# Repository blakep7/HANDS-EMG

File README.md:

# HANDS-EMG

**HANDS-EMG** is a real-time embedded system designed to read a user's EMG signals and classify their hand movements.

## Project Description
A battery-powered surface electromyography (sEMG) sensor system designed to classify hand movements based on the wearer's muscle activity.
The device utilizes four channels of wet electrodes placed on the user's forearm to capture sEMG signals.
These signals are processed through our procured analog front-end module operating at 2000Hz.
The digitized signals are transmitted to our microcontroller via SPI, where a machine learning algorithm classifies the hand movements based on a pre-trained model.
The system will output the movement classifications via USB, which can be visualized on a PC simulator.
Designed for efficiency, the device operates at a voltage of 3.7V provided by a rechargeable lithium polymer battery for portability.
The current ML model only classifies 3 hand movements: Wrist Flexion, Wrist Extension, and Fist Clench.

## Videos
[Project Overview (Entire Design Process)](https://www.youtube.com/watch?v=24S8prk70tI)

[Demo Video](https://www.youtube.com/watch?v=GeJwxeHSsiM)

## Team

- Blake Pearson
- Noah Marosok
- Kelly Hubbard
- Jayden Sumbillo
- Kirk Young

## About
Developed at **San Diego State University**.

**College of Engineering** -- **Department of Electrical and Computer Engineering (ECE)**

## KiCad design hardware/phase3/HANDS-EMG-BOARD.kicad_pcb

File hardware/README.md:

# PCB Projects
Welcome to the PCB repository! This folder contains four PCB phases:

- **Phase 1**
- **Phase 2**
- **Phase 3**

Each project is fully designed in KiCad and includes schematics, PCB layouts, and 3D models.

## Phase Descriptions

### Phase 1

**Description:**  
Contains 3 PCBs, each designed with a specific purpose.

**Key Components:**
- PMIC Board: Provide power to the following two PCBs
- ADS1299 Board: Our AFE board that handles processing and digitizing EMG signals
- STM32 Board: Our uC board that handles classification and compute

**Warnings**
- Do not use this phase, it taught us alot about PCB design but is riddled with issues
- PMIC Board is less than 50% functional.
    - 3.3V line is actually 3.6V which is absolute maximum of STM32
    - -2.5V line is unstable, due to only using a charge pump without a LDO after
- ADS1299 Board is not functional
    - Unknown issue in PCB design that kills the IC.

### Phase 2

**Description:**  
The team's attempt at a fully integrated PCB design.

**Warnings**
- Do not use this phase
- Board's USB to UART is not functional, no communication possible
- SWD footprint is mirrored

### Phase 3 (Final Phase)

**Description:**
The team's final design. Focused on simplicity, cost, and small dimensions. Fully tested and working

**Key Components**
- STM32L0: Our main compute, has the ML model and classifies the signals
- ADS1299: Our AFE, handles amplifying and digitizing our EMG signals
- FT231X: USB->UART IC for simple communication between STM32 and PC

---

## 3D Model Previews

**Final PCB 3D View:**  

---

## How to Open the Projects

1. Install [KiCad](https://kicad.org/) (v9).
2. Open KiCad and navigate to the respective folder (`phase3`).
3. Open the `.kicad_pro` project file inside each folder.

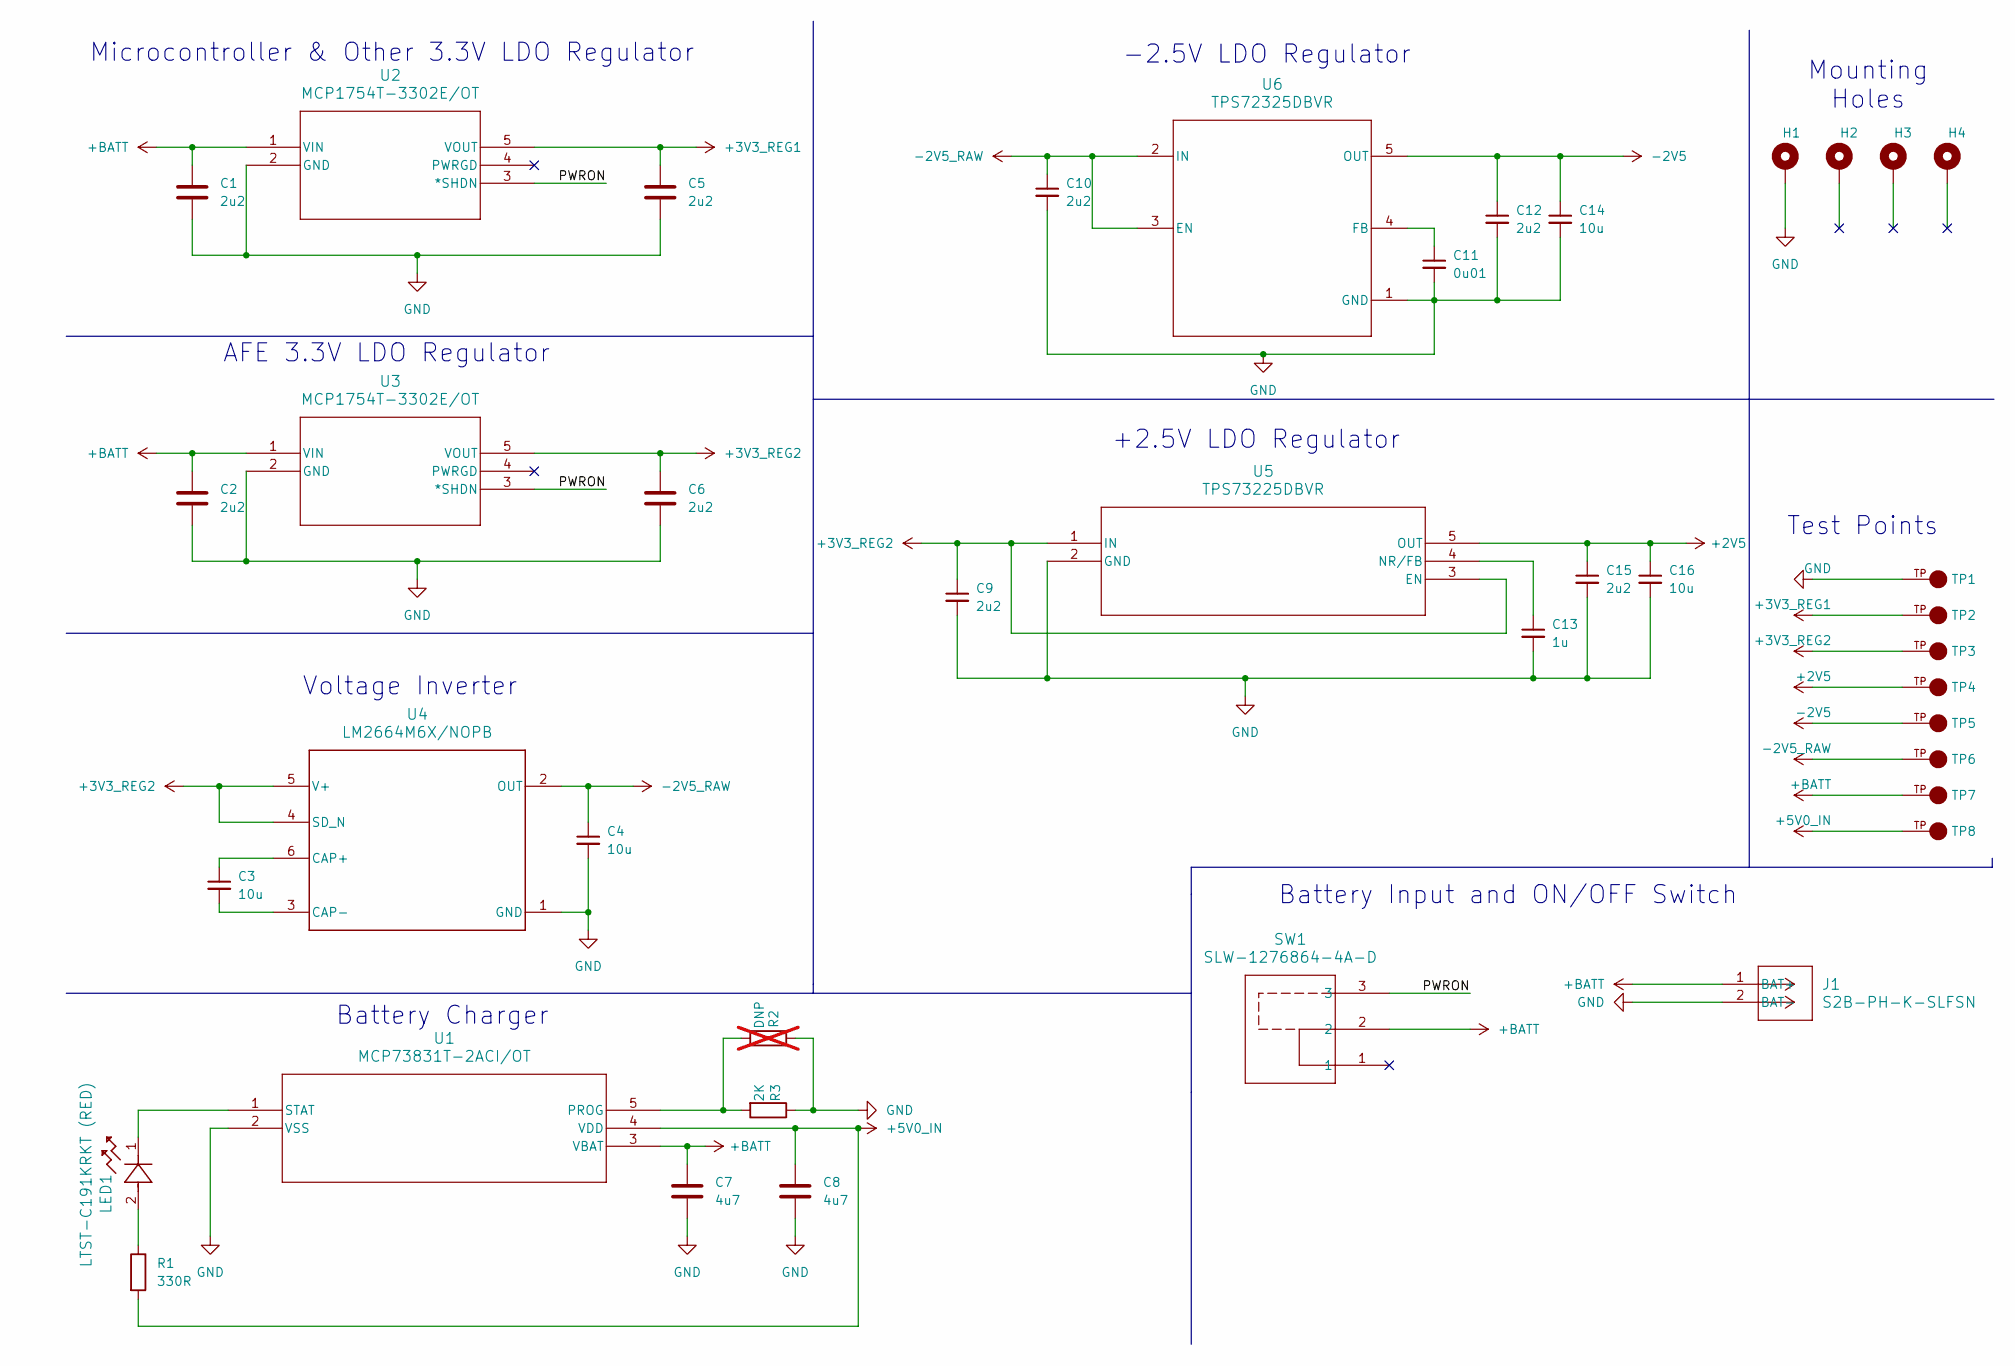
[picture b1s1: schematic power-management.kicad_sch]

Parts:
C1, C2, C5, C6, C9, C10, C12, C15: 2u2; C_0402_1005Metric
C3, C4, C14, C16: 10u; C_0603_1608Metric
C7, C8: 4u7; C_0603_1608Metric
C11: 0u01; C_0402_1005Metric
C13: 1u; C_0402_1005Metric
H1, H2, H3, H4: MountingHole_Pad; MountingHole_2.2mm_M2_Pad
J1: S2B-PH-K-SLFSN; S2B-PH-K-S
LED1: LTST-C191KRKT (RED); LTST-C191KRKT
R1: 330R; R_0603_1608Metric
R2: DNP; R_0603_1608Metric; not fitted
R3: 2K; R_0603_1608Metric
SW1: SLW-1276864-4A-D
TP1, TP2, TP3, TP4, TP5, TP6, TP7, TP8: 5015; PARTREV F
U1: MCP73831T-2ACI/OT; MCP73831T-2ACI-OT
U2, U3: MCP1754T-3302E/OT; MCP1754T-3302E-OT
U4: LM2664M6X/NOPB; LM2664M6X-NOPB
U5: TPS73225DBVR
U6: TPS72325DBVR

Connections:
+2V5: C15.1, C16.1, TP4.TP, U5.5 (OUT); also elsewhere on the board
+3V3_REG1: C5.1, TP2.TP, U2.5 (VOUT); also elsewhere on the board
+3V3_REG2: C6.1, C9.1, TP3.TP, U3.5 (VOUT), U4.4 (SD_N), U4.5 (V+), U5.1 (IN), U5.3 (EN); also elsewhere on the board
+5V0_IN: C8.1, R1.2, TP8.TP, U1.4 (VDD); also elsewhere on the board
+BATT: C1.1, C2.1, C7.1, J1.1 (BAT+), SW1.2, TP7.TP, U1.3 (VBAT), U2.1 (VIN), U3.1 (VIN)
-2V5: C12.1, C14.1, TP5.TP, U6.5 (OUT); also elsewhere on the board
-2V5_RAW: C4.1, C10.1, TP6.TP, U4.2 (OUT), U6.2 (IN), U6.3 (EN)
/Power-Management/PWRON: SW1.3, U2.3 (*SHDN), U3.3 (*SHDN)
GND: C1.2, C2.2, C4.2, C5.2, C6.2, C7.2, C8.2, C9.2, C10.2, C11.2, C12.2, C13.2, C14.2, C15.2, C16.2, H1.1, J1.2 (BAT-), R2.1, R3.1, TP1.TP, U1.2 (VSS), U2.2 (GND), U3.2 (GND), U4.1 (GND), U5.2 (GND), U6.1 (GND); also elsewhere on the board
unnamed: LED1.2, R1.1
unnamed: R2.2, R3.2, U1.5 (PROG)
unnamed: LED1.1, U1.1 (STAT)
unnamed: C3.1, U4.6 (CAP+)
unnamed: C3.2, U4.3 (CAP-)
unnamed: C13.1, U5.4 (NR/FB)
unnamed: C11.1, U6.4 (FB)

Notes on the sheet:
Battery Charger
+2.5V LDO Regulator
AFE 3.3V LDO Regulator
Test Points
Mounting Holes
-2.5V LDO Regulator
Voltage Inverter
Microcontroller & Other 3.3V LDO Regulator
Battery Input and ON/OFF Switch

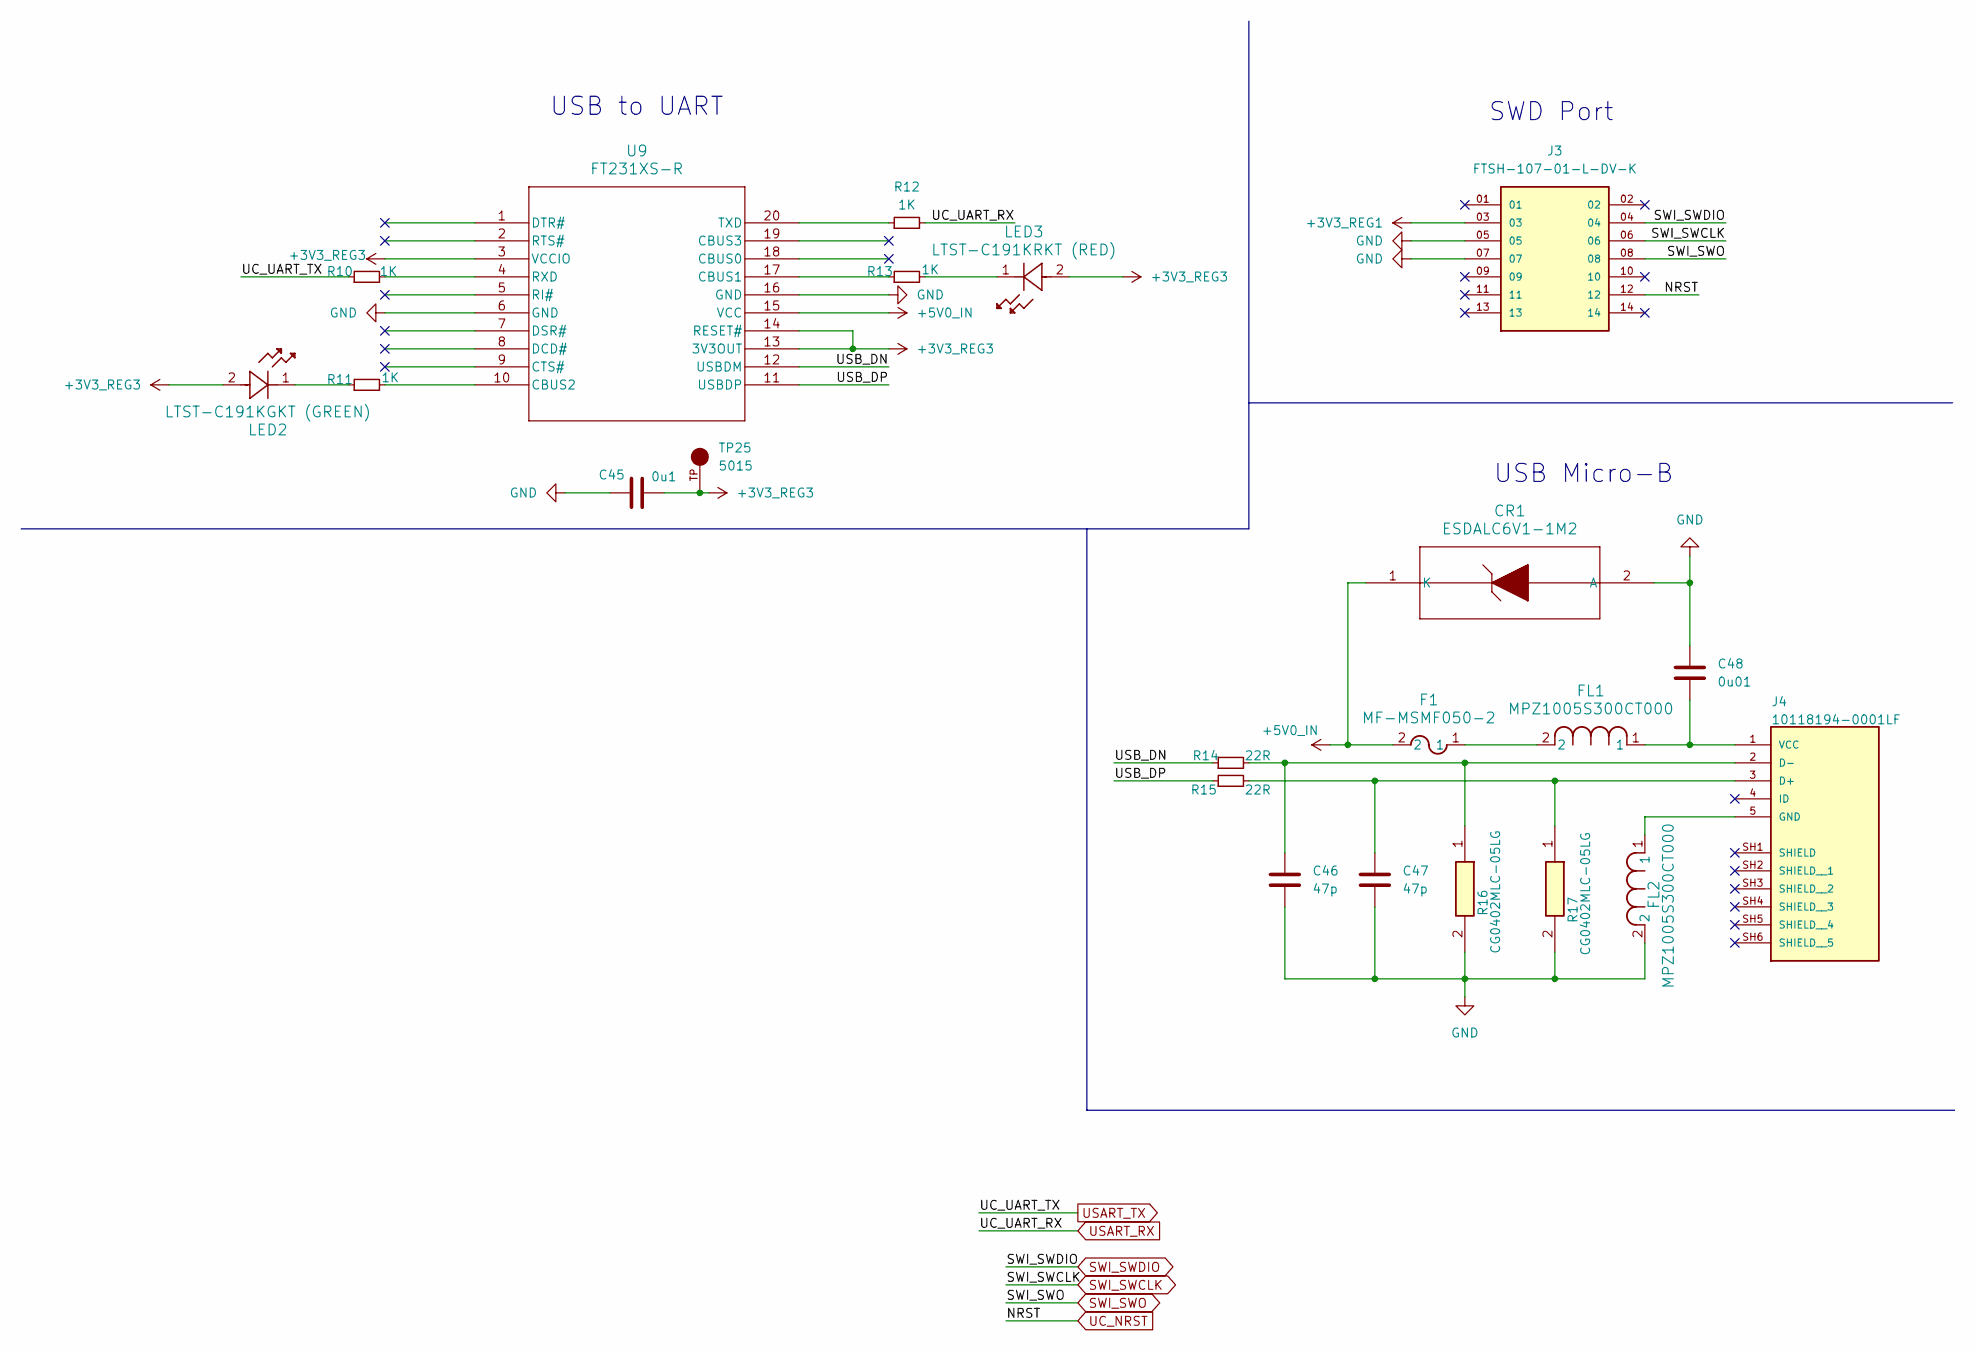
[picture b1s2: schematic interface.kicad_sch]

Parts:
C45: 0u1; C_0402_1005Metric
C46, C47: 47p; C_0402_1005Metric
C48: 0u01; C_0402_1005Metric
CR1: ESDALC6V1-1M2
F1: MF-MSMF050-2
FL1, FL2: MPZ1005S300CT000
J3: FTSH-107-01-L-DV-K; PARTREV R
J4: 10118194-0001LF; PARTREV D
LED2: LTST-C191KGKT (GREEN); LTST-C191KGKT
LED3: LTST-C191KRKT (RED); LTST-C191KRKT
R10, R11, R12, R13: 1K; R_0603_1608Metric
R14, R15: 22R; R_0402_1005Metric
R16, R17: CG0402MLC-05LG
TP25: 5015; PARTREV F
U9: FT231XS-R

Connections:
+3V3_REG1: J3.03; also elsewhere on the board
+3V3_REG3: C45.2, LED2.2, LED3.2, TP25.TP, U9.3 (VCCIO), U9.13 (3V3OUT), U9.14 (RESET#)
+5V0_IN: CR1.1 (K), F1.2, U9.15 (VCC); also elsewhere on the board
/Interface/USB_DN: R14.1, U9.12 (USBDM)
/Interface/USB_DP: R15.1, U9.11 (USBDP)
GND: C45.1, C46.2, C47.2, C48.1, CR1.2 (A), FL2.2, J3.05, J3.07, R16.2, R17.2, U9.6 (GND), U9.16 (GND); also elsewhere on the board
unnamed: F1.1, FL1.2
unnamed: C47.1, J4.3 (D+), R15.2, R17.1
unnamed: C46.1, J4.2 (D-), R14.2, R16.1
unnamed: FL2.1, J4.5 (GND)
unnamed: C48.2, FL1.1, J4.1 (VCC)
unnamed: LED2.1, R11.1
unnamed: LED3.1, R13.2
unnamed: R13.1, U9.17 (CBUS1)
unnamed: R11.2, U9.10 (CBUS2)
unnamed: R10.2, U9.4 (RXD)
unnamed: R12.1, U9.20 (TXD)
SWI_SWCLK: J3.06; also elsewhere on the board
SWI_SWDIO: J3.04; also elsewhere on the board
SWI_SWO: J3.08; also elsewhere on the board
UC_NRST: J3.12; also elsewhere on the board
USART_RX: R12.2; also elsewhere on the board
USART_TX: R10.1; also elsewhere on the board

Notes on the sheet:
USB Micro-B
USB to UART
SWD Port

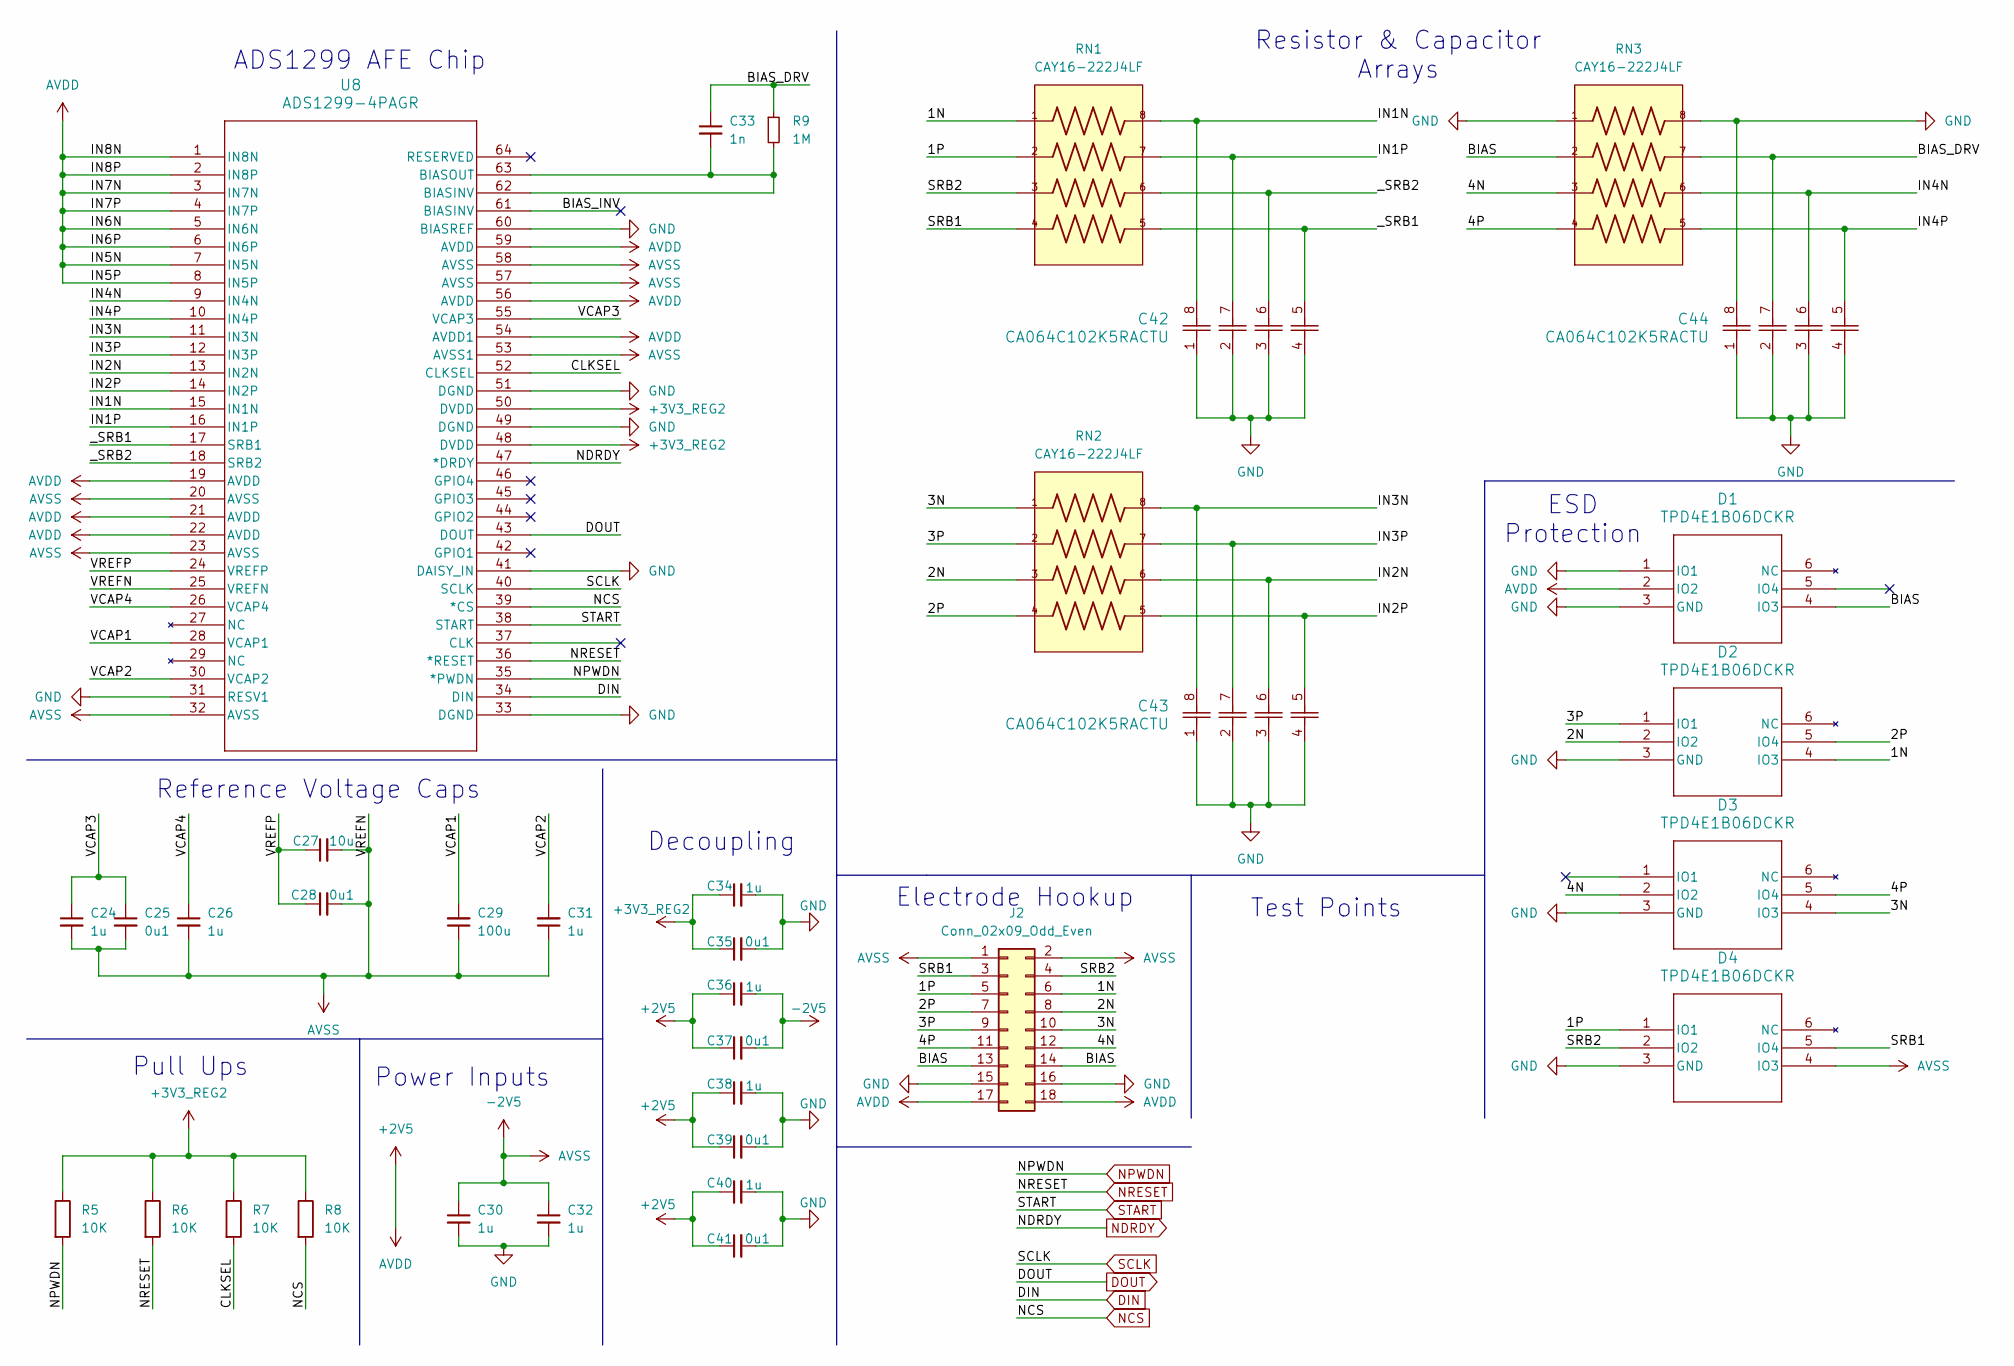
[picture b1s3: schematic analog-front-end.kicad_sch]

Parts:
C24, C26, C30, C31, C32, C34, C36, C38, C40: 1u; C_0402_1005Metric
C25, C28, C35, C37, C39, C41: 0u1; C_0402_1005Metric
C27: 10u; C_0603_1608Metric
C29: 100u; C_1206_3216Metric
C33: 1n; C_0402_1005Metric
C42, C43, C44: CA064C102K5RACTU; CA064C102K5RAC7800
D1, D2, D3, D4: TPD4E1B06DCKR
J2: Conn_02x09_Odd_Even; PinHeader_2x09_P2.54mm_Horizontal
R5, R6, R7, R8: 10K; R_0402_1005Metric
R9: 1M; R_0402_1005Metric
RN1, RN2, RN3: CAY16-222J4LF
U8: ADS1299-4PAGR

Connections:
+2V5: C36.1, C37.1, C38.1, C39.1, C40.1, C41.1, D1.2 (IO2), J2.17, J2.18, U8.1 (IN8N), U8.2 (IN8P), U8.3 (IN7N), U8.4 (IN7P), U8.5 (IN6N), U8.6 (IN6P), U8.7 (IN5N), U8.8 (IN5P), U8.19 (AVDD), U8.21 (AVDD), U8.22 (AVDD), U8.54 (AVDD1), U8.56 (AVDD), U8.59 (AVDD); also elsewhere on the board
+3V3_REG2: C34.1, C35.1, R5.1, R6.1, R7.1, R8.1, U8.48 (DVDD), U8.50 (DVDD); also elsewhere on the board
-2V5: C24.2, C25.2, C26.2, C27.2, C28.2, C29.1, C30.1, C31.1, C32.1, C36.2, C37.2, D4.4 (IO3), J2.1, J2.2, U8.20 (AVSS), U8.23 (AVSS), U8.25 (VREFN), U8.32 (AVSS), U8.53 (AVSS1), U8.57 (AVSS), U8.58 (AVSS); also elsewhere on the board
/Analog-Front-End/1N: D2.4 (IO3), J2.6, RN1.1
/Analog-Front-End/1P: D4.1 (IO1), J2.5, RN1.2
/Analog-Front-End/2N: D2.2 (IO2), J2.8, RN2.3
/Analog-Front-End/2P: D2.5 (IO4), J2.7, RN2.4
/Analog-Front-End/3N: D3.4 (IO3), J2.10, RN2.1
/Analog-Front-End/3P: D2.1 (IO1), J2.9, RN2.2
/Analog-Front-End/4N: D3.2 (IO2), J2.12, RN3.3
/Analog-Front-End/4P: D3.5 (IO4), J2.11, RN3.4
/Analog-Front-End/BIAS: D1.4 (IO3), J2.13, J2.14, RN3.2
/Analog-Front-End/BIAS_DRV: C33.1, C44.7, R9.1, RN3.7
/Analog-Front-End/BIAS_INV: U8.61 (BIASINV)
/Analog-Front-End/CLKSEL: R7.2, U8.52 (CLKSEL)
/Analog-Front-End/IN1N: C42.8, RN1.8, U8.15 (IN1N)
/Analog-Front-End/IN1P: C42.7, RN1.7, U8.16 (IN1P)
/Analog-Front-End/IN2N: C43.6, RN2.6, U8.13 (IN2N)
/Analog-Front-End/IN2P: C43.5, RN2.5, U8.14 (IN2P)
/Analog-Front-End/IN3N: C43.8, RN2.8, U8.11 (IN3N)
/Analog-Front-End/IN3P: C43.7, RN2.7, U8.12 (IN3P)
/Analog-Front-End/IN4N: C44.6, RN3.6, U8.9 (IN4N)
/Analog-Front-End/IN4P: C44.5, RN3.5, U8.10 (IN4P)
/Analog-Front-End/SRB1: D4.5 (IO4), J2.3, RN1.4
/Analog-Front-End/SRB2: D4.2 (IO2), J2.4, RN1.3
/Analog-Front-End/VCAP1: C29.2, U8.28 (VCAP1)
/Analog-Front-End/VCAP2: C31.2, U8.30 (VCAP2)
/Analog-Front-End/VCAP3: C24.1, C25.1, U8.55 (VCAP3)
/Analog-Front-End/VCAP4: C26.1, U8.26 (VCAP4)
/Analog-Front-End/VREFP: C27.1, C28.1, U8.24 (VREFP)
/Analog-Front-End/_SRB1: C42.5, RN1.5, U8.17 (SRB1)
/Analog-Front-End/_SRB2: C42.6, RN1.6, U8.18 (SRB2)
DIN: U8.34 (DIN); also elsewhere on the board
DOUT: U8.43 (DOUT); also elsewhere on the board
GND: C30.2, C32.2, C34.2, C35.2, C38.2, C39.2, C40.2, C41.2, C42.1, C42.2, C42.3, C42.4, C43.1, C43.2, C43.3, C43.4, C44.1, C44.2, C44.3, C44.4, C44.8, D1.1 (IO1), D1.3 (GND), D2.3 (GND), D3.3 (GND), D4.3 (GND), J2.15, J2.16, RN3.1, RN3.8, U8.31 (RESV1), U8.33 (DGND), U8.41 (DAISY_IN), U8.49 (DGND), U8.51 (DGND), U8.60 (BIASREF); also elsewhere on the board
NCS: R8.2, U8.39 (*CS); also elsewhere on the board
NDRDY: U8.47 (*DRDY); also elsewhere on the board
NPWDN: R5.2, U8.35 (*PWDN); also elsewhere on the board
NRESET: R6.2, U8.36 (*RESET); also elsewhere on the board
unnamed: C33.2, R9.2, U8.62 (BIASINV), U8.63 (BIASOUT)
SCLK: U8.40 (SCLK); also elsewhere on the board
START: U8.38 (START); also elsewhere on the board

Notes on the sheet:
Pull Ups
Decoupling
Reference Voltage Caps
Electrode Hookup
Resistor & Capacitor Arrays
Test Points
ESD Protection
ADS1299 AFE Chip
Power Inputs

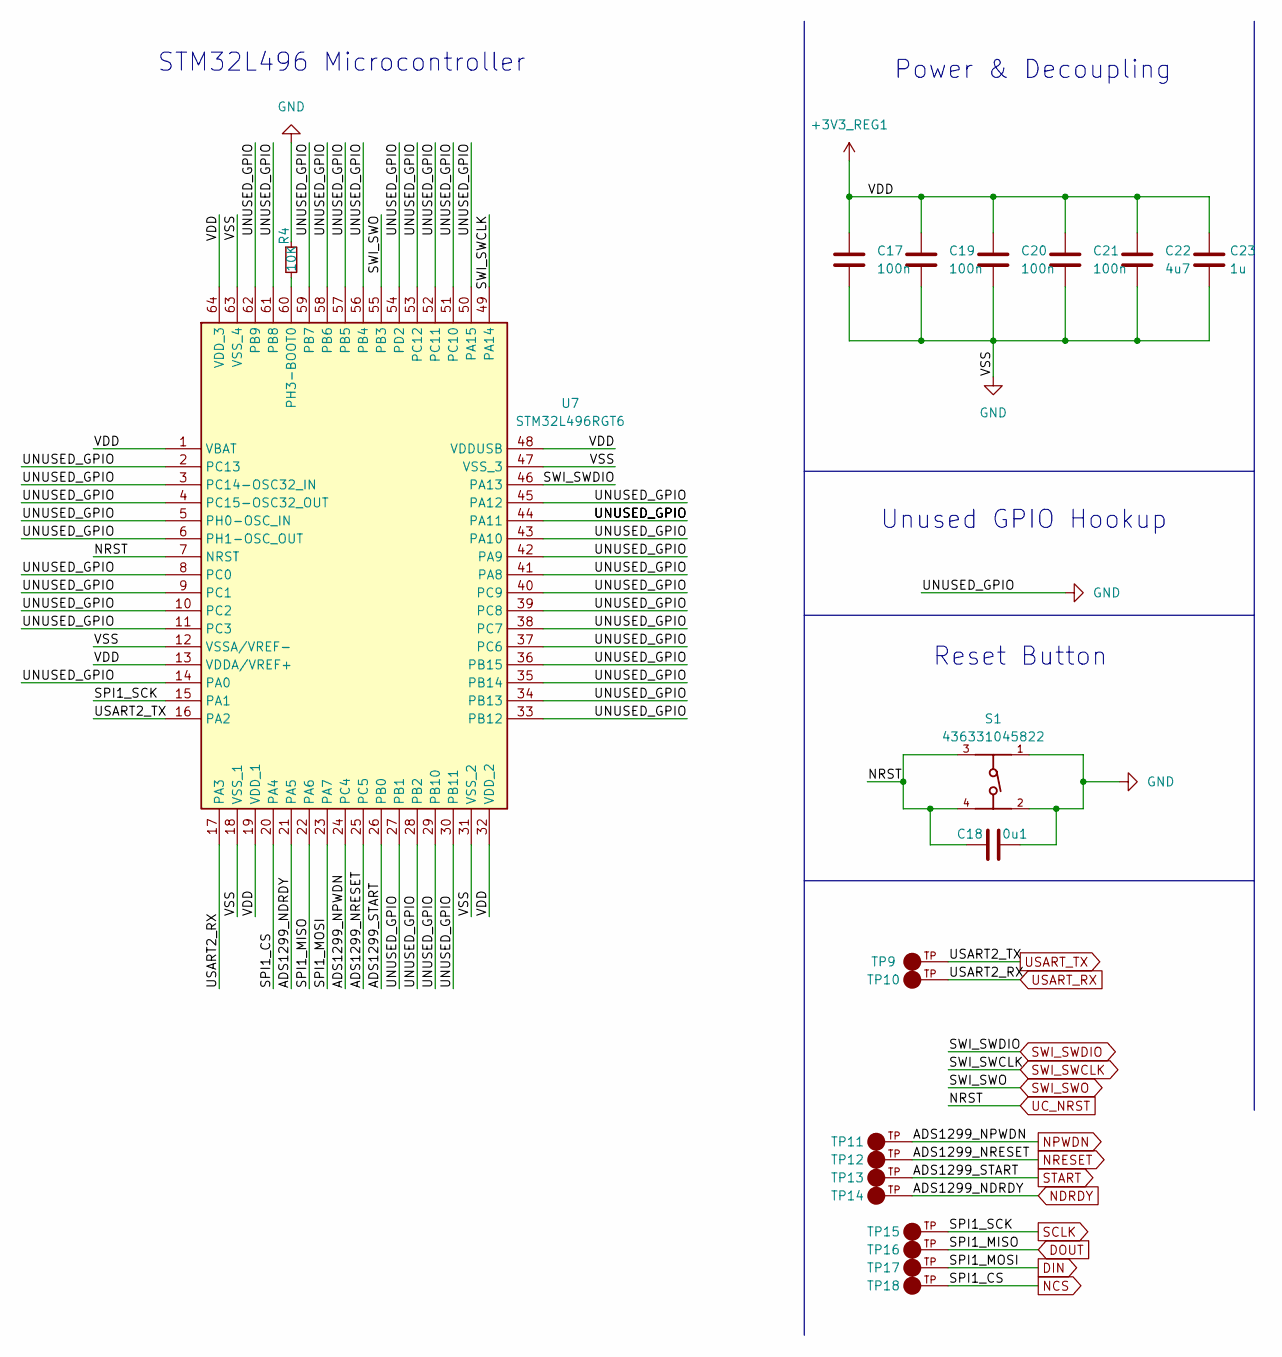
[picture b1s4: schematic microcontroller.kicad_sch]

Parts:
C17, C19, C20, C21: 100n; C_0603_1608Metric
C18: 0u1; C_0603_1608Metric
C22: 4u7; C_0603_1608Metric
C23: 1u; C_0603_1608Metric
R4: 10K; R_0402_1005Metric
S1: 436331045822
TP9, TP10, TP11, TP12, TP13, TP14, TP15, TP16, TP17, TP18: 5015; PARTREV F
U7: STM32L496RGT6; Manufacturer_Part_Number STM32L496RGT6; Mouser Part Number 511-STM32L496RGT6

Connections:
+3V3_REG1: C17.1, C19.1, C20.1, C21.1, C22.1, C23.1, U7.1 (VBAT), U7.13 (VDDA/VREF+), U7.19 (VDD_1), U7.32 (VDD_2), U7.48 (VDDUSB), U7.64 (VDD_3); also elsewhere on the board
DIN: TP17.TP, U7.23 (PA7); also elsewhere on the board
DOUT: TP16.TP, U7.22 (PA6); also elsewhere on the board
GND: C17.2, C18.1, C19.2, C20.2, C21.2, C22.2, C23.2, R4.1, S1.1, S1.2, U7.2 (PC13), U7.3 (PC14-OSC32_IN), U7.4 (PC15-OSC32_OUT), U7.5 (PH0-OSC_IN), U7.6 (PH1-OSC_OUT), U7.8 (PC0), U7.9 (PC1), U7.10 (PC2), U7.11 (PC3), U7.12 (VSSA/VREF-), U7.14 (PA0), U7.18 (VSS_1), U7.27 (PB1), U7.28 (PB2), U7.29 (PB10), U7.30 (PB11), U7.31 (VSS_2), U7.33 (PB12), U7.34 (PB13), U7.35 (PB14), U7.36 (PB15), U7.37 (PC6), U7.38 (PC7), U7.39 (PC8), U7.40 (PC9), U7.41 (PA8), U7.42 (PA9), U7.43 (PA10), U7.44 (PA11), U7.45 (PA12), U7.47 (VSS_3), U7.50 (PA15), U7.51 (PC10), U7.52 (PC11), U7.53 (PC12), U7.54 (PD2), U7.56 (PB4), U7.57 (PB5), U7.58 (PB6), U7.59 (PB7), U7.61 (PB8), U7.62 (PB9), U7.63 (VSS_4); also elsewhere on the board
NCS: TP18.TP, U7.20 (PA4); also elsewhere on the board
NDRDY: TP14.TP, U7.21 (PA5); also elsewhere on the board
NPWDN: TP11.TP, U7.24 (PC4); also elsewhere on the board
NRESET: TP12.TP, U7.25 (PC5); also elsewhere on the board
unnamed: R4.2, U7.60 (PH3-BOOT0)
SCLK: TP15.TP, U7.15 (PA1); also elsewhere on the board
START: TP13.TP, U7.26 (PB0); also elsewhere on the board
SWI_SWCLK: U7.49 (PA14); also elsewhere on the board
SWI_SWDIO: U7.46 (PA13); also elsewhere on the board
SWI_SWO: U7.55 (PB3); also elsewhere on the board
UC_NRST: C18.2, S1.3, S1.4, U7.7 (NRST); also elsewhere on the board
USART_RX: TP10.TP, U7.17 (PA3); also elsewhere on the board
USART_TX: TP9.TP, U7.16 (PA2); also elsewhere on the board

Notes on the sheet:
STM32L496 Microcontroller
Unused GPIO Hookup
Reset Button
Power & Decoupling

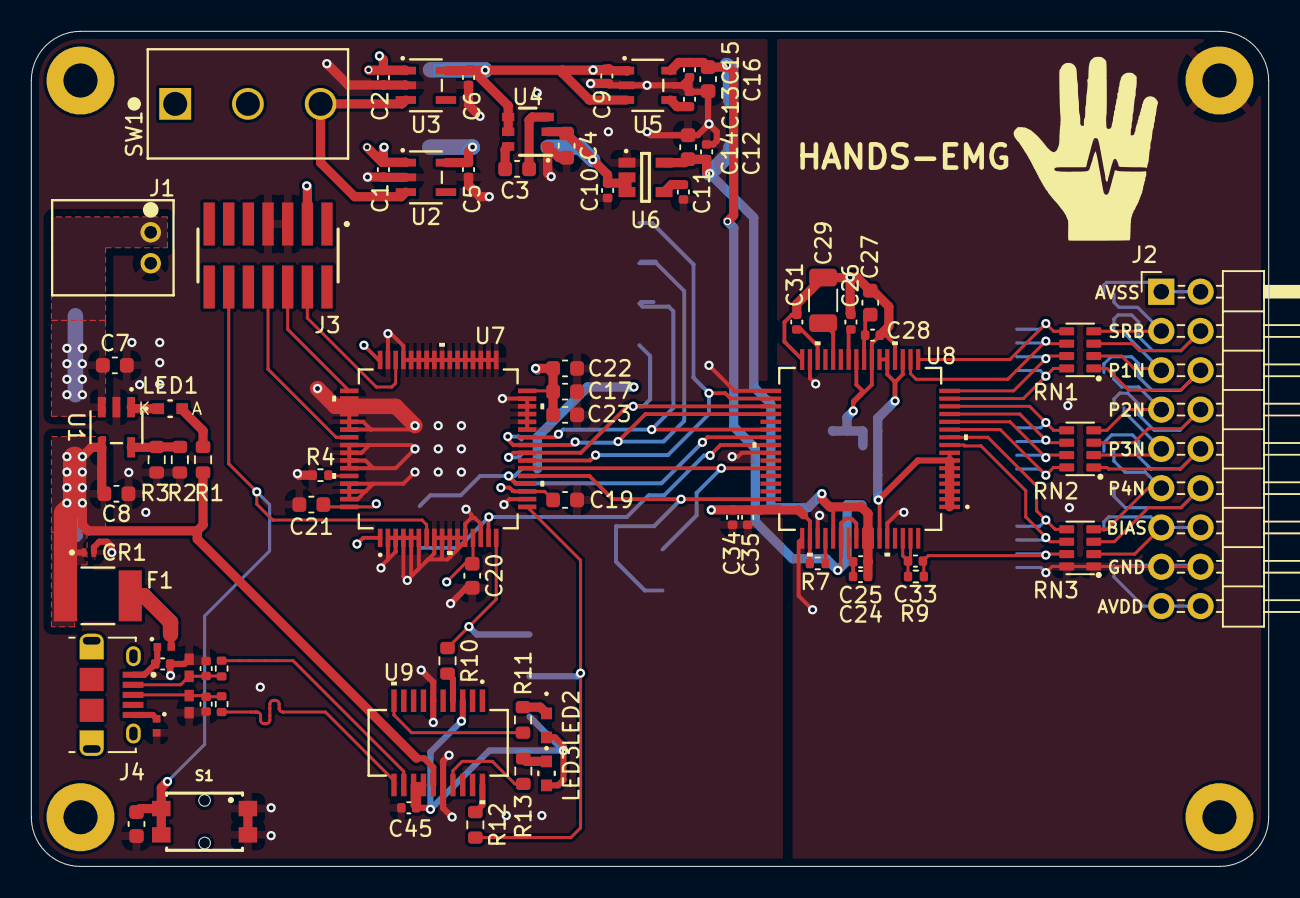
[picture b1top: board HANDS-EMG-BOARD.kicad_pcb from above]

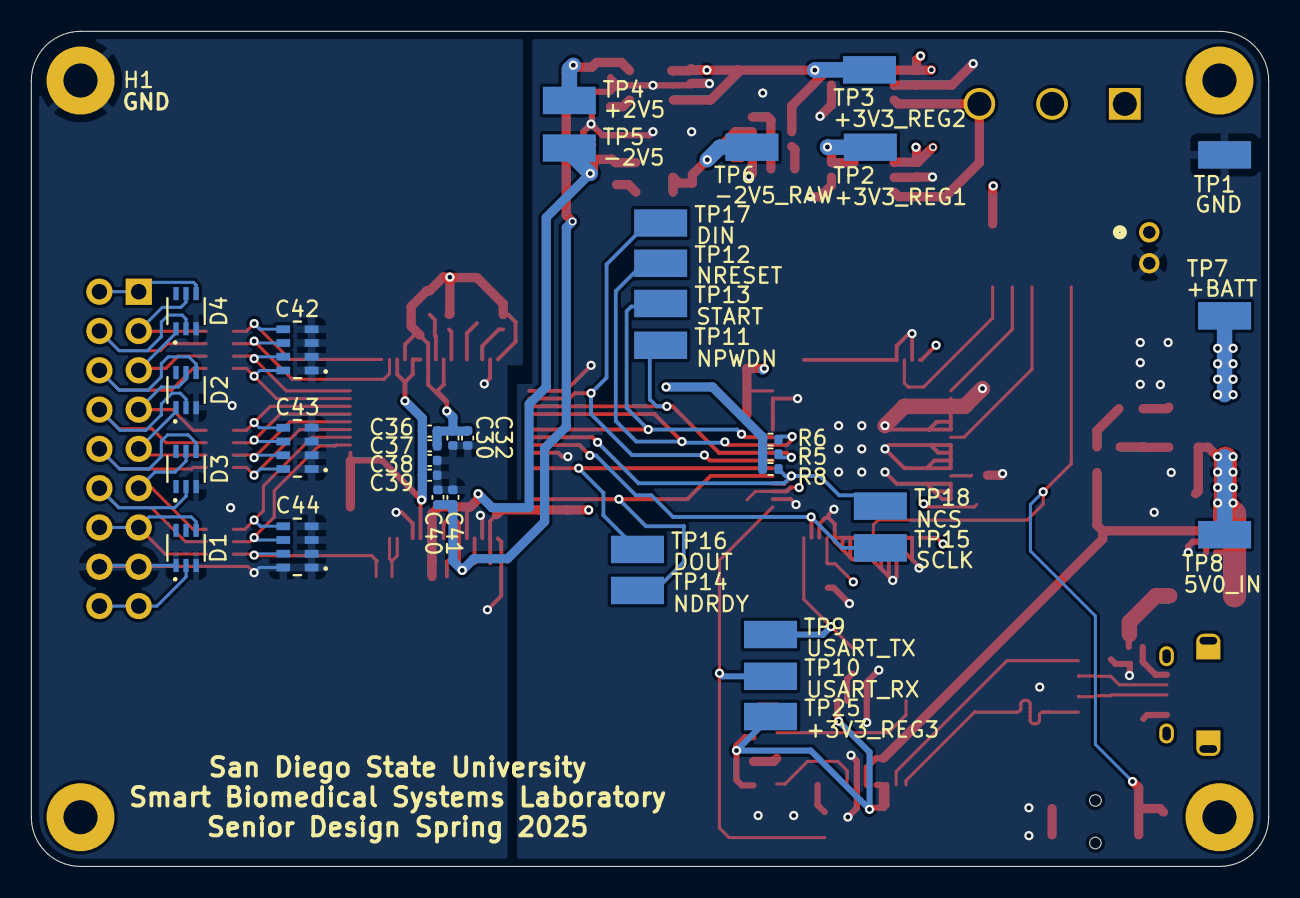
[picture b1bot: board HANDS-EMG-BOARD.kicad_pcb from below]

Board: 4 copper layers, 80.0 x 54.0 mm, 117 parts (37 on the bottom side), 74 nets.

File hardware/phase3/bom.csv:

Designator,Footprint,Quantity,Value,LCSC Part #,
"C1, C10, C12, C15, C2, C5, C6, C9",0402,8,2u2,,GRM155R61C225KE44D
"C11, C48",0402,2,0u01,,CC0402KRX7R7BB103
"C13, C24, C26, C30, C31, C32, C34, C36, C38, C40",0402,10,1u,,CC0402KRX7R5BB105
"C14, C16, C27, C3, C4",0603,5,10u,,GRM188C80G106KE47D
"C17, C19, C20, C21",0603,4,100n,,CC0603KRX7R7BB104
C18,0603,1,0u1,,CC0603KRX7R7BB104
"C22, C7, C8",0603,3,4u7,,CL10A475KP8NNNC
C23,0603,1,1u,,CC0603KRX7R5BB105
"C25, C28, C35, C37, C39, C41, C45",0402,7,0u1,,CC0402KRX7R7BB104
C29,1206,1,100u,,CC1206MKX5R5BB107
C33,0402,1,1n,,CC0402KRX7R7BB102
"C42, C43, C44",CA064C102K5RAC7800,3,CA064C102K5RACTU,,CA064C102K5RACTU
"C46, C47",0402,2,47p,,CC0402JRNPO9BN470
CR1,ESDALC6V1-1M2,1,ESDALC6V1-1M2,,ESDALC6V1-1M2
"D1, D2, D3, D4",TPD4E1B06DCKR,4,TPD4E1B06DCKR,,TPD4E1B06DCKR
F1,MF-MSMF050-2,1,MF-MSMF050-2,,MF-MSMF050-2
"FL1, FL2",MPZ1005S300CT000,2,MPZ1005S300CT000,,MPZ1005S300CT000
"H1, H2, H3, H4",MountingHole_2.2mm_M2_Pad,4,MountingHole_Pad,,DNP
J1,S2B-PH-K-S,1,S2B-PH-K-SLFSN,,S2B-PH-K-SLFSN
J2,PinHeader_2x09_P2.54mm_Horizontal,1,Conn_02x09_Odd_Even,,PH2RA-18-UA
J3,FTSH-107-01-L-DV-K,1,FTSH-107-01-L-DV-K,,FTSH-107-01-L-DV-K
J4,10118194-0001LF,1,10118194-0001LF,,10118194-0001LF
"LED1, LED3",LTST-C191KRKT,2,LTST-C191KRKT (RED),,LTST-C191KRKT (RED)
LED2,LTST-C191KGKT,1,LTST-C191KGKT (GREEN),,LTST-C191KGKT (GREEN)
R1,0603,1,330R,,RC0603JR-07330RL
"R10, R11, R12, R13",0603,4,1K,,RC0603FR-071KL
"R14, R15",0402,2,22R,,RC0402FR-0722RL
"R16, R17",CG0402MLC-05LG,2,CG0402MLC-05LG,,CG0402MLC-05LG
R2,0603,1,DNP,,DNP
R3,0603,1,2K,,RC0603FR-072KL
"R4, R5, R6, R7, R8",0402,5,10K,,ERJ-2RKF1002X
R9,0402,1,1M,,RC0402JR-071ML
"RN1, RN2, RN3",CAY16-222J4LF,3,CAY16-222J4LF,,CAY16-222J4LF
S1,4.36331E+11,1,4.36331E+11,,4.36331E+11
SW1,SLW-1276864-4A-D,1,SLW-1276864-4A-D,,SLW-1276864-4A-D
"TP1, TP10, TP11, TP12, TP13, TP14, TP15, TP16, TP17, TP18, TP2, TP25, TP3, TP4, TP5, TP6, TP7, TP8, TP9",5015,19,5015,,5015
U1,MCP73831T-2ACI-OT,1,MCP73831T-2ACI/OT,,MCP73831T-2ACI/OT
"U2, U3",MCP1754T-3302E-OT,2,MCP1754T-3302E/OT,,MCP1754T-3302E/OT
U4,LM2664M6X-NOPB,1,LM2664M6X/NOPB,,LM2664M6X/NOPB
U5,TPS73225DBVR,1,TPS73225DBVR,,TPS73225DBVR
U6,TPS72325DBVR,1,TPS72325DBVR,,TPS72325DBVR
U7,STM32L496RGT6,1,STM32L496RGT6,,STM32L496RGT6
U8,ADS1299-4PAGR,1,ADS1299-4PAGR,,ADS1299-4PAGR
U9,FT231XS-R,1,FT231XS-R,,FT231XS-R
